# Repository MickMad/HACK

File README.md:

#HACK
##HackAday Cortex Kit

A Cortex-M0+ development kit with an Atmel SAM R21, a USB device/host port, a regulator, some passives, a programming header, and breakout headers.

```
Copyright © Michele Perla 2015

This documentation describes Open Hardware and is licensed under the CERN OHL v. 1.2.
You may redistribute and modify this documentation under the terms of the CERN OHL v.1.2. 
(http://ohwr.org/cernohl). This documentation is distributed
WITHOUT ANY EXPRESS OR IMPLIED WARRANTY, INCLUDING OF
MERCHANTABILITY, SATISFACTORY QUALITY AND FITNESS FOR A
PARTICULAR PURPOSE. Please see the CERN OHL v.1.2 for applicable
conditions
```

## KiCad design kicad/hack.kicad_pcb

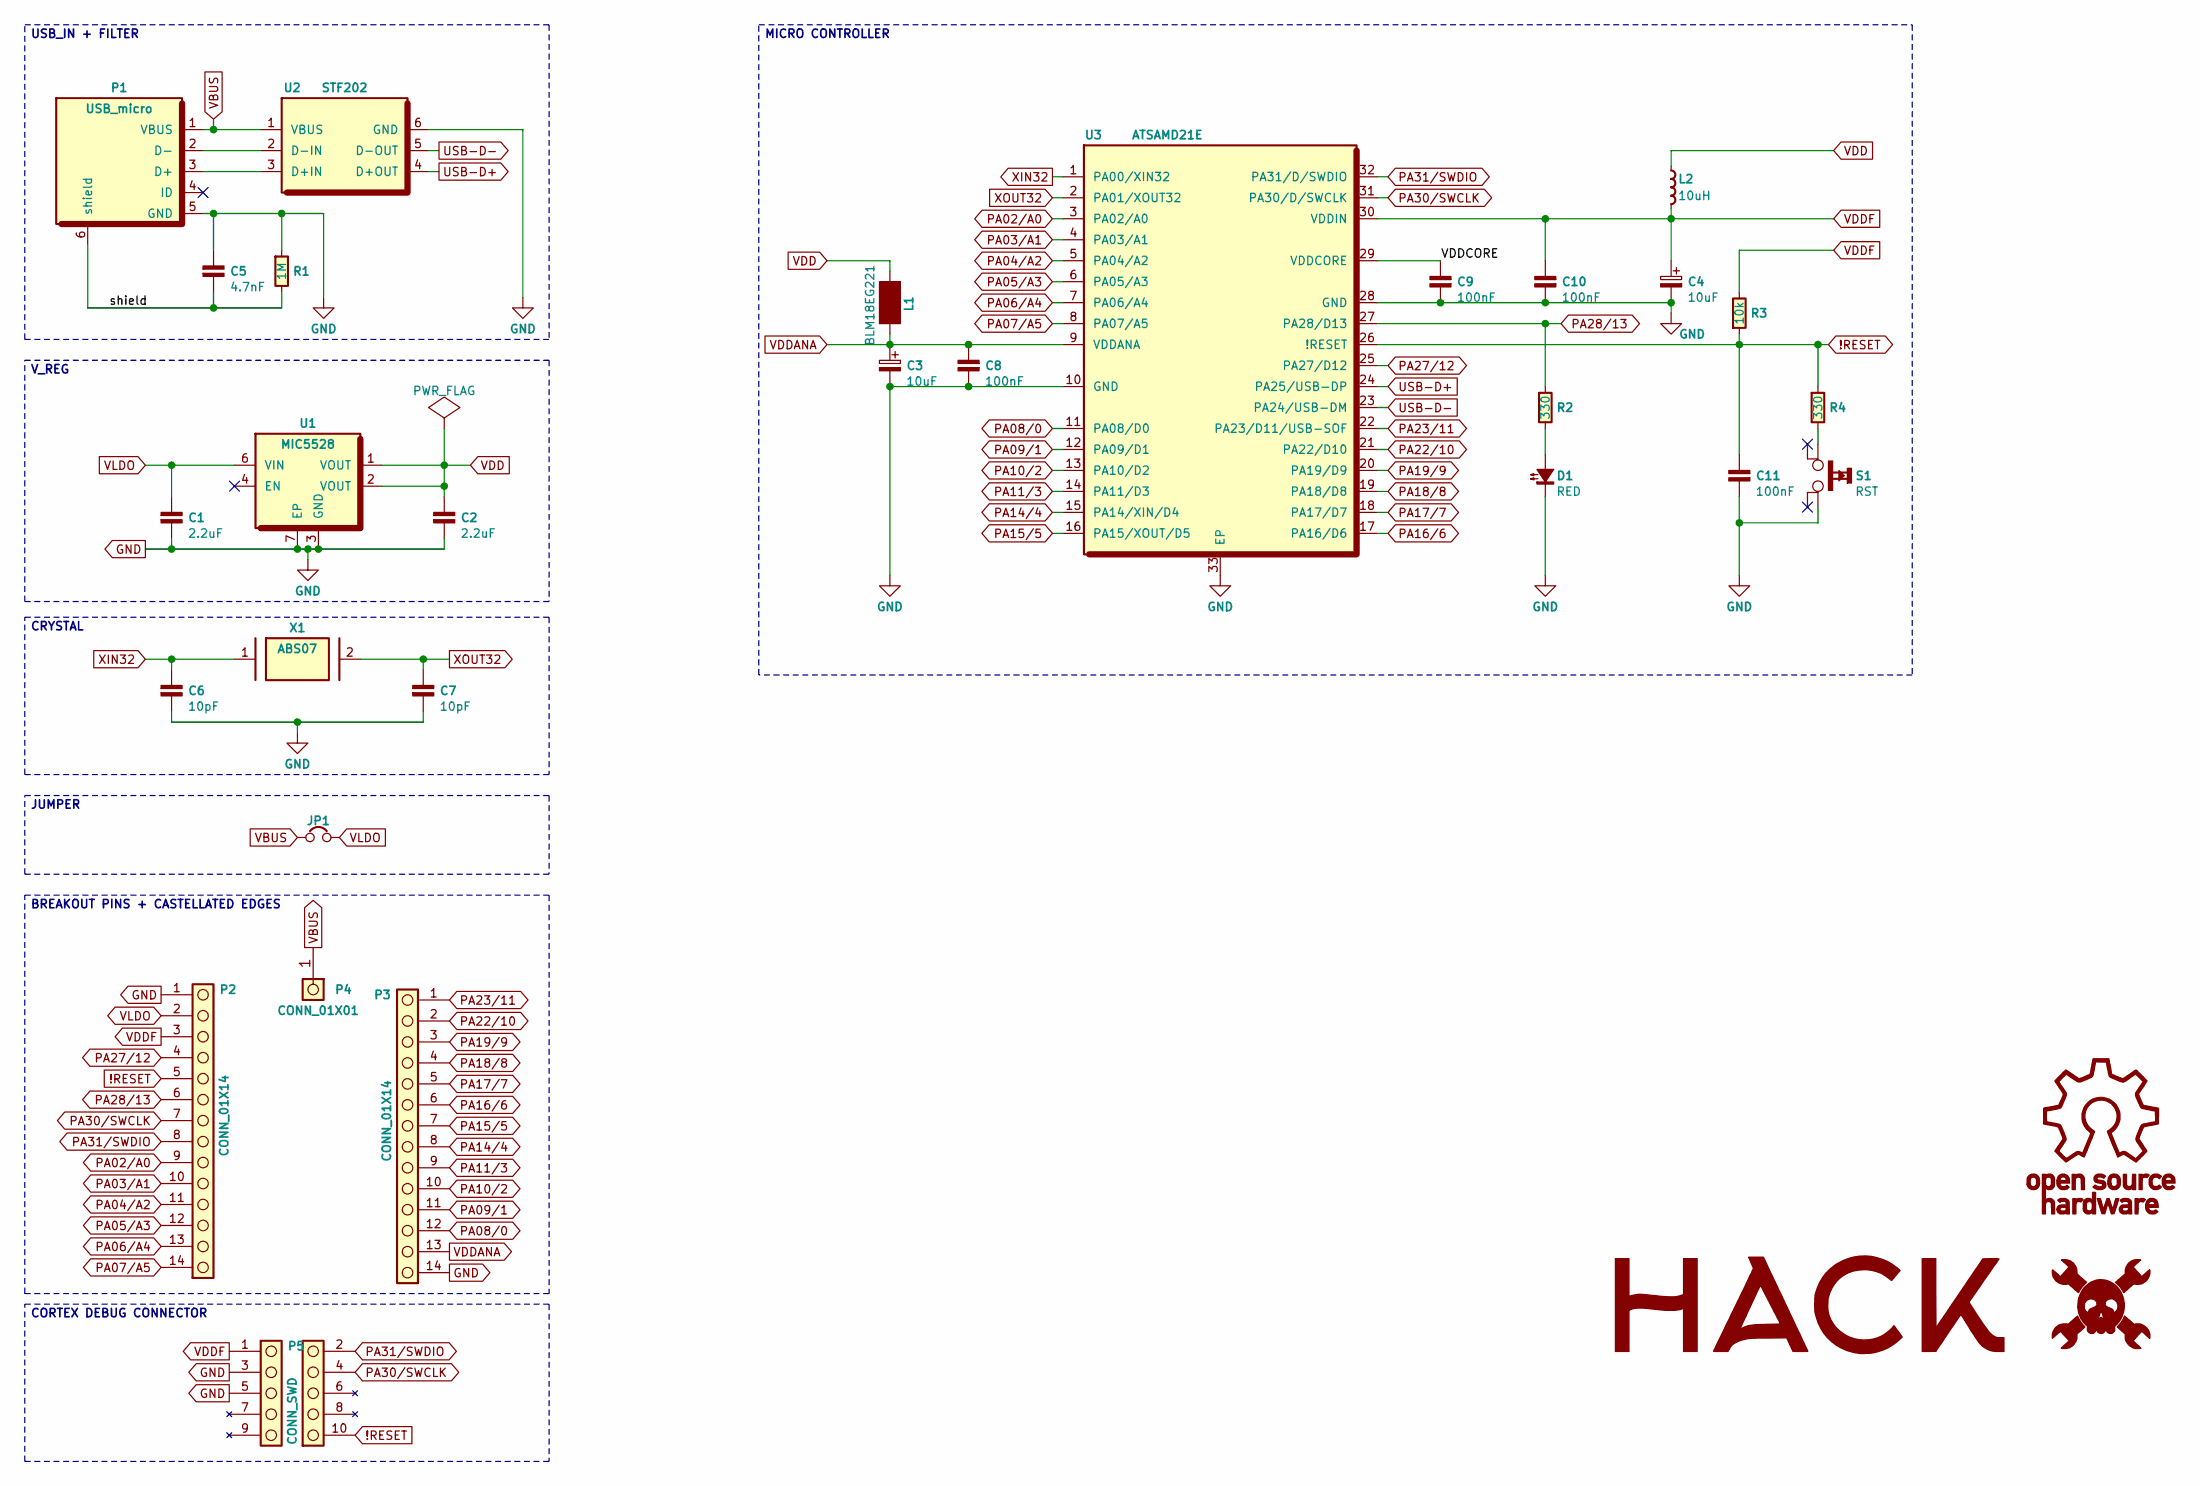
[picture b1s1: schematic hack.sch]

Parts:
C1, C2: 2.2uF; C_0603
C3, C4: 10uF; CAP_ELEC_SMD_3x5mm
C5: 4.7nF; C_0603
C6, C7: 10pF; C_0603
C8, C9, C10, C11: 100nF; C_0603
D1: RED; LED_0603
JP1: Jumper_NO_Small; SMD_Jumper
L1: BLM18EG221; L_0603
L2: 10uH; ELLVFG
LOGO1: OSHW; OSHW-LOGO
LOGO2: HACKADAY; HACKADAY-LOGO
LOGO3: HACK; HACK-LOGO
P1: USB_micro; ST-USB-001G
P2, P3: CONN_01X14; Pin_Castellated_1x14
P4: CONN_01X01; Pin_Castellated_1x01
P5: CONN_SWD; Cortex_Debug_Connector_50mils
R1: 1M; R_0603
R2, R4: 330; R_0603
R3: 10k; R_0603
S1: RST; SPST-PTS_810
U1: MIC5528; DFN-6-1EP_1.2x1.2mm_Pitch0.4mm
U2: STF202; TSOP-6
U3: ATSAMD21E; QFN-32-1EP_5x5mm_Pitch0.5mm
X1: ABS07; xtal_3.2x1.5mm

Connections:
!RESET: C11.1, P2.5, P5.10 (nRESET), R3.1, R4.1, U3.26 (!RESET)
/VDDCORE: C9.1, U3.29 (VDDCORE)
/shield: C5.2, P1.6 (shield), R1.2
GND: C1.2, C2.2, C3.2, C4.2, C5.1, C6.2, C7.2, C8.2, C9.2, C10.2, C11.2, D1.2 (K), P1.5 (GND), P2.1, P3.14, P5.3 (GND), P5.5 (GND), R1.1, S1.1, U1.3 (GND), U1.7 (EP), U2.6 (GND), U3.10 (GND), U3.28 (GND), U3.33 (EP)
unnamed: D1.1 (A), R2.2
unnamed: P1.2 (D-), U2.2 (D-IN)
unnamed: P1.3 (D+), U2.3 (D+IN)
unnamed: R4.2, S1.3
PA02/A0: P2.9, U3.3 (PA02/A0)
PA03/A1: P2.10, U3.4 (PA03/A1)
PA04/A2: P2.11, U3.5 (PA04/A2)
PA05/A3: P2.12, U3.6 (PA05/A3)
PA06/A4: P2.13, U3.7 (PA06/A4)
PA07/A5: P2.14, U3.8 (PA07/A5)
PA08/0: P3.12, U3.11 (PA08/D0)
PA09/1: P3.11, U3.12 (PA09/D1)
PA10/2: P3.10, U3.13 (PA10/D2)
PA11/3: P3.9, U3.14 (PA11/D3)
PA14/4: P3.8, U3.15 (PA14/XIN/D4)
PA15/5: P3.7, U3.16 (PA15/XOUT/D5)
PA16/6: P3.6, U3.17 (PA16/D6)
PA17/7: P3.5, U3.18 (PA17/D7)
PA18/8: P3.4, U3.19 (PA18/D8)
PA19/9: P3.3, U3.20 (PA19/D9)
PA22/10: P3.2, U3.21 (PA22/D10)
PA23/11: P3.1, U3.22 (PA23/D11/USB-SOF)
PA27/12: P2.4, U3.25 (PA27/D12)
PA28/13: P2.6, R2.1, U3.27 (PA28/D13)
PA30/SWCLK: P2.7, P5.4 (SWDCLK), U3.31 (PA30/D/SWCLK)
PA31/SWDIO: P2.8, P5.2 (SWDIO), U3.32 (PA31/D/SWDIO)
USB-D+: U2.4 (D+OUT), U3.24 (PA25/USB-DP)
USB-D-: U2.5 (D-OUT), U3.23 (PA24/USB-DM)
VBUS: JP1.1, P1.1 (VBUS), P4.1, U2.1 (VBUS)
VDD: C2.1, L1.1, L2.1, U1.1 (VOUT), U1.2 (VOUT)
VDDANA: C3.1, C8.1, L1.2, P3.13, U3.9 (VDDANA)
VDDF: C4.1, C10.1, L2.2, P2.3, P5.1 (VTref), R3.2, U3.30 (VDDIN)
VLDO: C1.1, JP1.2, P2.2, U1.6 (VIN)
XIN32: C6.1, U3.1 (PA00/XIN32), X1.1
XOUT32: C7.1, U3.2 (PA01/XOUT32), X1.2

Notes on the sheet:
USB_IN + FILTER
V_REG
CRYSTAL
JUMPER
BREAKOUT PINS + CASTELLATED EDGES
MICRO CONTROLLER
CORTEX DEBUG CONNECTOR

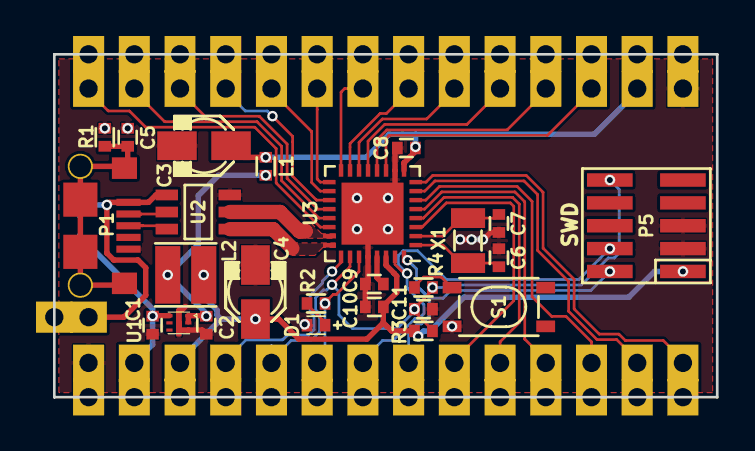
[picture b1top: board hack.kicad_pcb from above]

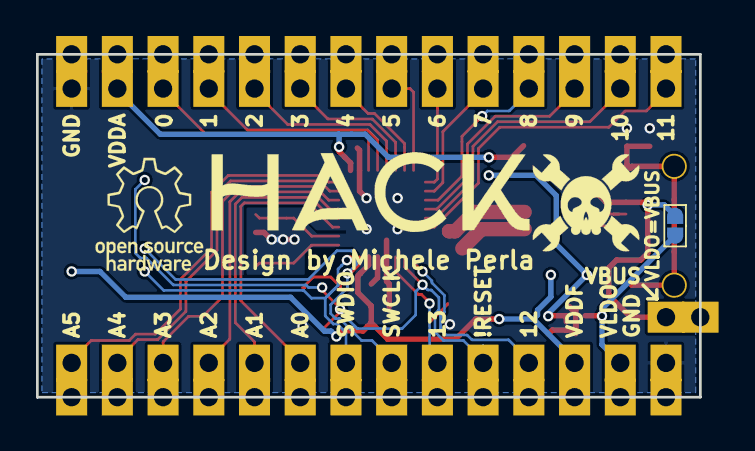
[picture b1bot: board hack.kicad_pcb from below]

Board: 2 copper layers, 36.8 x 19.1 mm, 32 parts (6 on the bottom side), 39 nets.

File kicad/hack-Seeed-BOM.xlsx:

Refs | Value | Desc | Footprint | Manf | Manufacturer Part No | Qty | Unit$ | Ext$ | minQty | minQtyPrice | SKU to ORDER | real price | order from | NOTES
C1,C2 | 2.2uF |  | hack-footprints:C_0603_HandSoldering |  | CC0603MRX5R5BB225 | 2 | 5.0799999999999998E-2 | 2.032 |  |  | 40 | 2.032 | Digikey
C3,C4 | 10uF |  | hack-footprints:c_elec_3x5.3 |  | UWX1C100MCL2GB | 2 | 0.13400000000000001 | 5.36 |  |  | 40 | 5.36 | Digikey
C5 | 4.7nF |  | hack-footprints:C_0603_HandSoldering |  | 302010144 | 1 | 0.01 | 0.2 | 100 | 1 | 1 | 1 | Seeed
C6,C7 | 10pF |  | hack-footprints:C_0603_HandSoldering |  | 302010097 | 2 | 0.01 | 0.4 | 100 | 1 | 1 | 1 | Seeed
C8-C11 | 100nF |  | hack-footprints:C_0603_HandSoldering |  | 302010138 | 4 | 0.02 | 1.6 | 100 | 2 | 1 | 2 | Seeed
D1 | RED |  | hack-footprints:LED_0603_HandSoldering |  | 304090042 | 1 | 0.03 | 0.6 | 50 | 1.5 | 1 | 1.5 | Seeed
L1 | BLM18EG221 |  | hack-footprints:L_0603_HandSoldering |  | BLM18EG221SN1D | 1 | 0.10299999999999999 | 2.06 |  |  | 20 | 2.06 | Digikey
L2 | 10uH |  | hack-footprints:ELLVFG |  | ELL-VFG100MC | 1 | 0.21199999999999999 | 4.24 |  |  | 20 | 4.24 | Digikey
P1 | USB_micro |  | hack-footprints:ST-USB-001G |  | 10118193-0001LF | 1 | 0.3 | 6 | 10 | 3 | 1 | 3 | Digikey
P2,P3 | CONN_01X14 |  | hack-footprints:Pin_Castellated_1x13 |  | 320020128 | 1 | 0.08 | 3.2 | 30 | 2.4 | 1 | 2.4 | Seeed | PLACEHOLDER, end user will cut the header (40 positions) and solder it
P5 | CONN_SWD |  |  |  | 320020119 | 1 | 0.2036 |  |  |  |  |  | Seeed
R1 | 1M |  | hack-footprints:R_0603_HandSoldering |  | 301010151 | 1 | 0.01 | 0.2 | 100 | 1 | 1 | 1 | Seeed
R2,R4 | 330 |  | hack-footprints:R_0603_HandSoldering |  | 301010300 | 2 | 0.01 | 0.4 | 100 | 1 | 1 | 1 | Seeed
R3 | 10k |  | hack-footprints:R_0603_HandSoldering |  | 301010299 | 1 | 0.01 | 0.2 | 100 | 1 | 1 | 1 | Seeed
S1 | RST |  | hack-footprints:SPST-PTS_810 |  | 311020045 | 1 | 0.2036 | 4.0720000000000001 | 10 | 2.036 | 1 | 2.036 | Seeed
U1 | MIC5528 |  | hack-footprints:DFN-6-1EP_1.2x1.2mm_Pitch0.4mm |  | MIC5528-3.3YMT-TR | 1 | 0.187 | 3.74 |  |  | 20 | 3.74 | Digikey
U2 | STF202 |  | hack-footprints:TSOP-6 |  | STF202-22T1G | 1 | 0.49199999999999999 | 9.84 |  |  | 20 | 9.84 | Digikey
U3 | ATSAMD21E |  | hack-footprints:QFN-32-1EP_5x5mm_Pitch0.5mm |  | ATSAMD21E18A-MU | 1 | 3.04 | 60.8 |  |  | 20 | 60.8 | Digikey
X1 | ABS07 |  | hack-footprints:xtal_3.2x1.5mm |  | 306010055 | 1 | 0.35 | 7 | 5 | 1.75 | 1 | 1.75 | Seeed

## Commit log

2015-08-31 :neckbeard: Added .gitattributes & .gitignore files
2015-10-05 Second commit
2015-10-08 Finishing layout, added PCB antenna
2015-10-12 Third commit
    Changed cutout of PCB so that one side hosts the antenna; moved part of
    the header to the right side (use a female receptacle instead of a male
    header to retain breadboard usability)
2015-10-12 Added temp EAGLE CAD files to .gitignore
2015-10-12 Added impedance controlled microstrips
    Added impedance controlled microstrips (diff. impedance of 100 Ohms from
    chip to balun, single ended impedance of 50 Ohms from balun to antenna)
2015-10-13 1st revision board is done
2015-10-14 3D model added
    It's missing the balun and the 32.768 KHz crystal models only
2015-12-21 Migrating project to KiCAD
2015-12-23 Final components placement almost done
    During this phase I checked if everything could fit in the board. It
    didn't, so I found a replacement LDO (in a small 1.2x1.2mm DFN package)
    that needs 2x0603 ceramic caps rather than two clunky electros (more
    free space then) and I finally changed the D21E package to QFN as well,
    now everything seems to fit quite well.
2015-12-24 Layout 99,9% finished
    Nets 100% routed, need to double check if copper pours are all connected
    to ground; added fiducials on board (for pick-n-place machines), I only
    need to find a good spot for them
2015-12-28 Cleaning up before test run
    Removed obsolete Eagle CAD files, added OSHW/Hackaday logos on schematic
    and silkscreen, removed ground connections for pins 2-3 of 32.768 KHz
    XTAL, removed traces under USB data lines, moving analog lines around
    (not beneath) XTAL (w.i.p.), moved components names on silkscreen to be
    readable, set fiducials in position, fixed SPST SMD package
2015-12-29 Layout 100% completed, cosmetics not yet
2016-01-04 Finished silkscreen cosmetics, added gerbers
2016-01-05 Added castellated pins
2016-01-05 Fixed gerbers (silkcreen issue with one pin)
2016-01-05 Changed USB connector package, revised layout
2016-01-05 Updated GERBER files, removed DRC errors in PCB
2016-01-05 fresh PDF and Gerbers in separate folders. Step/VRML files ready for 3D render
2016-01-06 FreeCAD 3D render in Fabricate dir, moved gerber dir nested under kicad
2016-01-06 Added datasheets, manufacturer numbers field for every component
2016-01-06 Updated KiCost BOM file w manf# field
2016-01-06 Added pin header datasheet+manf# (15 pins instead of 13 because 15 is cheaper)
2016-01-07 added 3d model for ELL-VFG and some other minor edits
2016-01-07 Added Seeedstudio costs for some components in schematic, changed 2.2uF manf# field to real manufacturer number instead of Seeedstudio SKU
2016-01-07 Updated Seeedstudio cost information
2016-01-07 Fixed KiCost BOM issue, updated BOM
2016-01-07 Updated BOM, added sheet fixed for 20 boards
    Usefult for test run purposes
2016-01-07 Updated BOM
2016-01-08 Added secondary USB connector footprint
    Previous one is only available from Seeedstudio, this one is from FCI
    and available from all distributors
2016-01-08 Changed LED, headers, USBmicro, XTAL manf#
    These parts are readily available from all distributors, previous ones
    were only sold by Seeed
2016-01-08 Updated BOMs
    One contains normally available parts numbers (hack-Digi-BOM), the other
    contains mostly Seeedstudio-sourced parts numbers (hack-Seeed-BOM)
2016-01-18 Optimized footprints, freed some PCB real estate
2016-01-18 Updated fabrication files
2016-01-18 Updated BOM (re-runned KiCost to check today's price)
2016-01-18 Fixed gerbers (outline was in all layers)
2016-01-18 Fixed PCB (not connected LED ground), updated fab files accordingly
2016-01-18 Updated pcb+gerber (via was still missing from D1 to GND)
2016-01-18 fresh gerber and seeed BoM for ready for prototype
2016-01-19 added Freecad 3d model for ELL-VFG inductor
2016-01-20 Added VBUS pin, GND pin near VDDANA
2016-01-21 test commit
2016-01-21 Reducing board size (w.i.p.)
2016-01-22 Reduced overall board size
2016-01-22 Fixed footprints refereneces on top silkscreen
2016-01-22 Added back gerber files zip
2016-01-25 Form factor is PDIP-24 now, ready to fab
    HACK now fits a PDIP-24 package (its solderable thru-hole headers
    spacing is now 0.6"); being longer there's some space on the top side,
    so it now features a convenient Cortex SWD Connector, a 2x5 male pin
    header with 50 mils spacing in SMD package.
2016-01-28 fresh 3D model and graphics
2016-03-22 new 3D models from Maurice with open source license
2016-07-13 Add 1-click-bom and kitnic.yaml
2016-08-13 Change image links to be relative to repo root
